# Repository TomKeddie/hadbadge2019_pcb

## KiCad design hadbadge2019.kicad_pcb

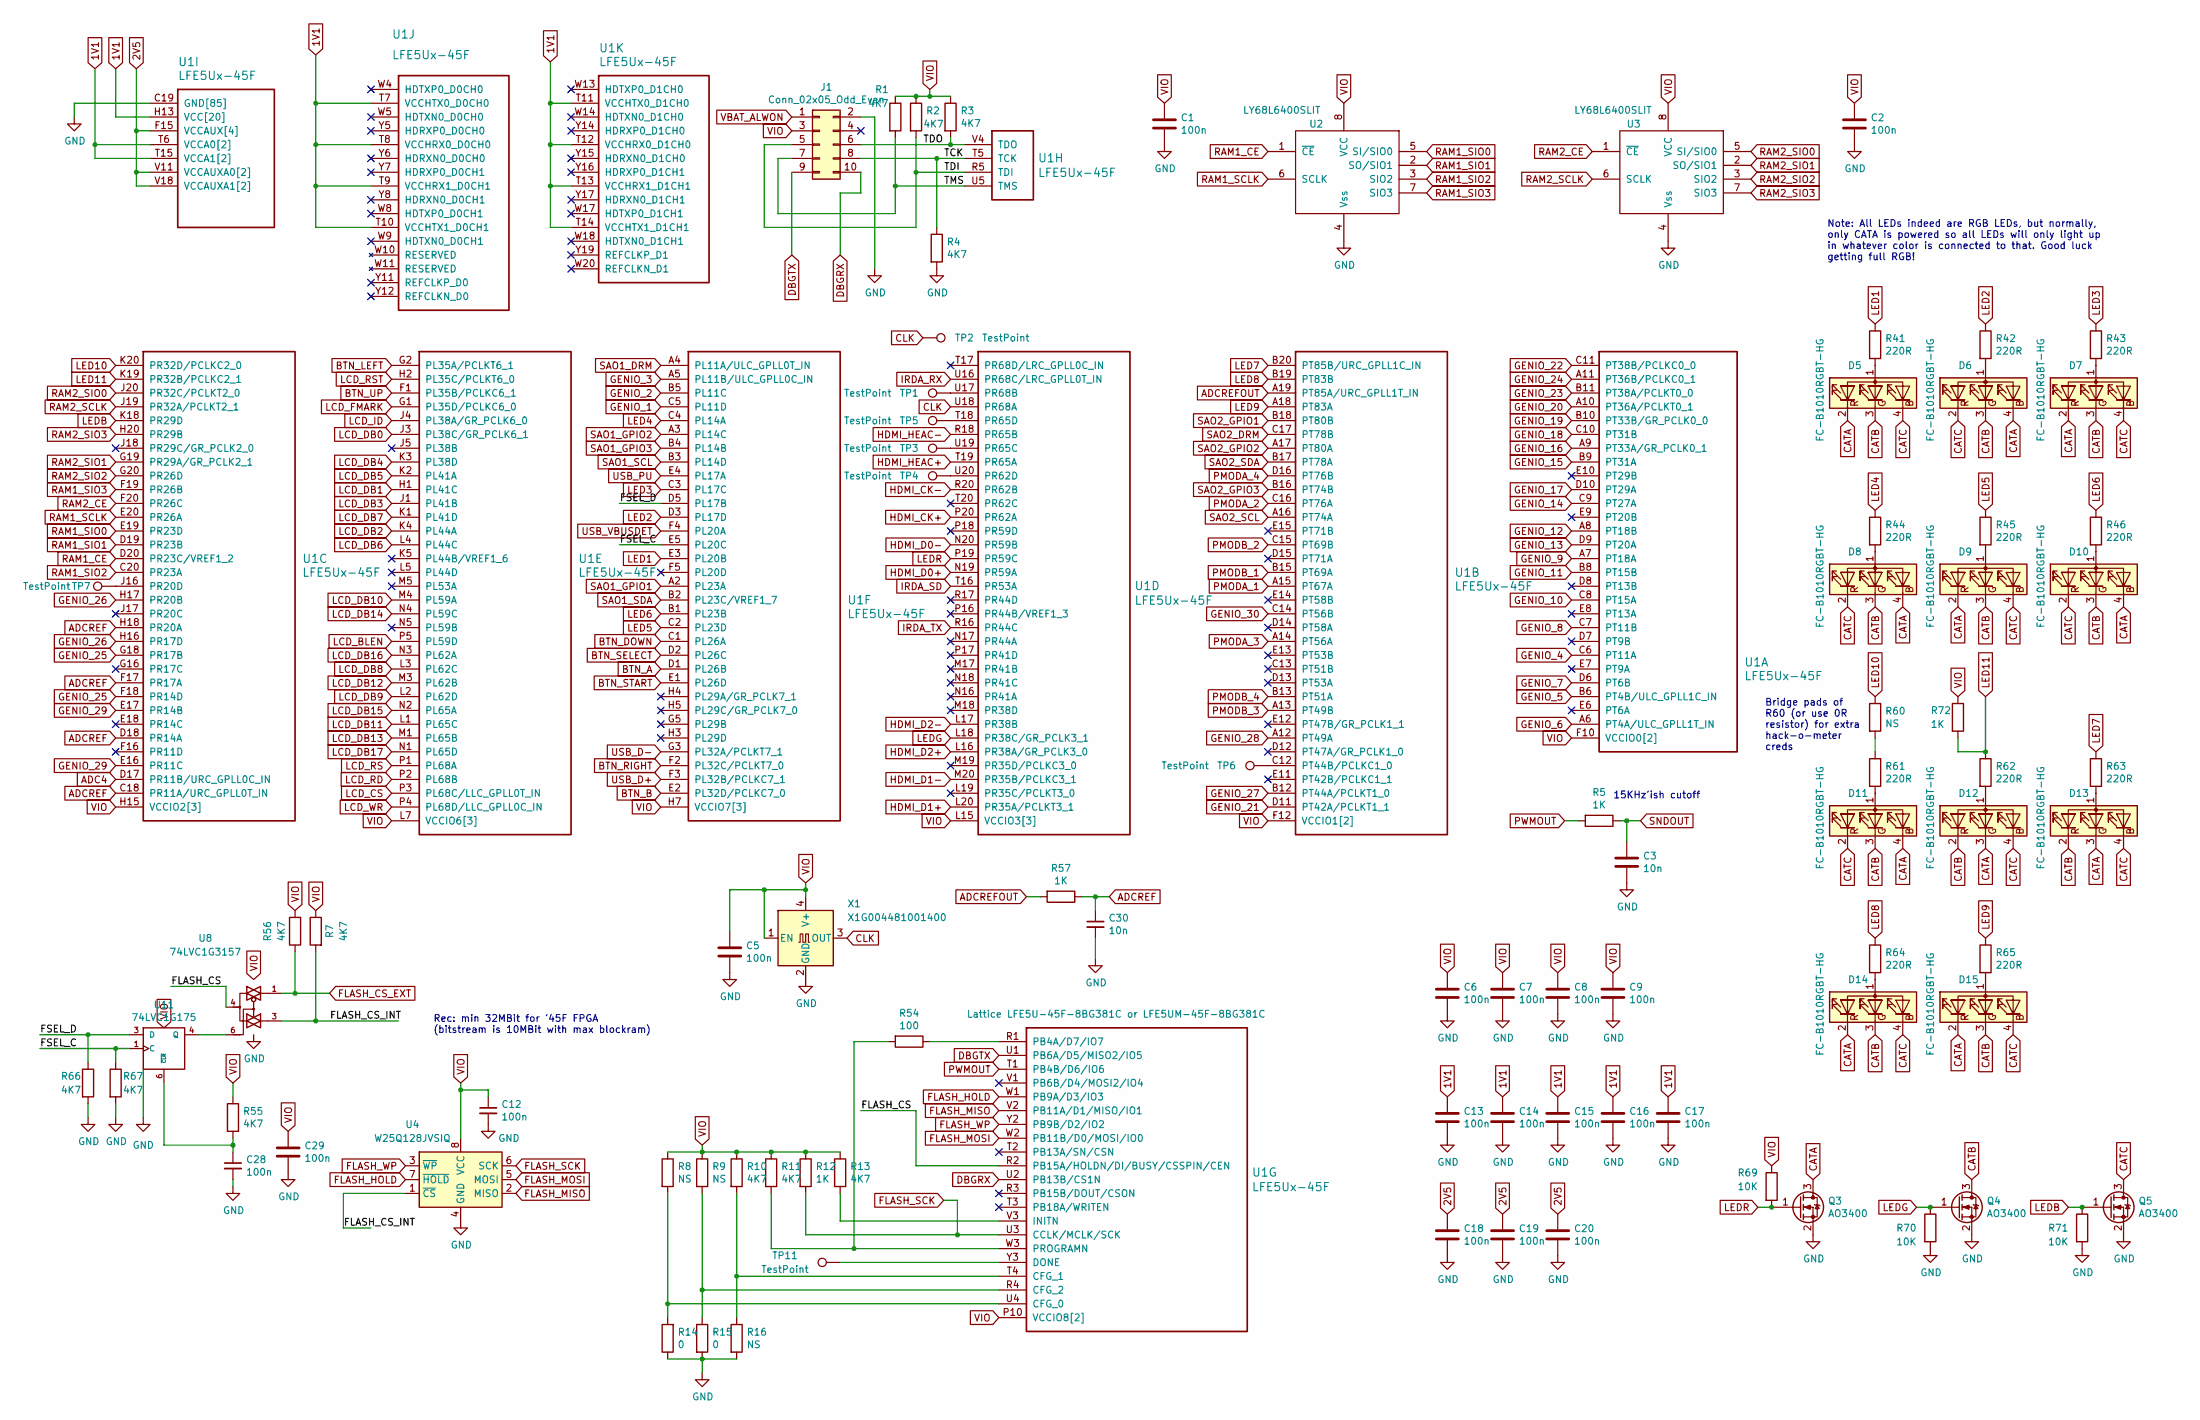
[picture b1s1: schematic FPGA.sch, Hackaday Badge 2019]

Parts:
C1, C2, C5, C6, C7, C8, C9, C12, C13, C14, C15, C16, C17, C18, C19, C20, C28, C29: 100n; C_0603_1608Metric
C3, C30: 10n; C_0603_1608Metric
D5, D6, D7, D8, D9, D10, D11, D12, D13, D14, D15: FC-B1010RGBT-HG
J1: Conn_02x05_Odd_Even; PinHeader_2x05_P2.54mm_Vertical
Q3, Q4, Q5: AO3400; SOT-23
R1, R2, R3, R4, R7, R10, R11, R13, R55, R56, R66, R67: 4K7; R_0603_1608Metric
R5, R12, R57, R72: 1K; R_0603_1608Metric
R8, R9, R16, R60: NS; R_0603_1608Metric
R14, R15: 0; R_0603_1608Metric
R41, R42, R43, R44, R45, R46, R61, R62, R63, R64, R65: 220R; R_0603_1608Metric
R54: 100; R_0603_1608Metric
R69, R70, R71: 10K; R_0603_1608Metric
TP1, TP2, TP3, TP4, TP5, TP6, TP7, TP11: TestPoint; TestPoint_Pad_D1.0mm
U1: LFE5Ux-45F; Lattice_caBGA-381_17.0x17.0mm_Layout20x20_P0.8mm_Ball0.4mm_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
U2, U3: LY68L6400SLIT; SSOP-8_3.9x5.05mm_P1.27mm
U4: W25Q128JVSIQ; SSOP-8_5.25x5.24mm_P1.27mm
U8: 74LVC1G3157; SOT-23-6
U11: 74LVC1G175; SOT-23-6
X1: X1G004481001400; Seiko_fp_crystal_SMD_7050-4Pin_7.0x5.0mm

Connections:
1V1: C13.1, C14.1, C15.1, C16.1, C17.1, U1.H8 (VCC[20]), U1.H9 (VCC[20]), U1.H10 (VCC[20]), U1.H11 (VCC[20]), U1.H12 (VCC[20]), U1.H13 (VCC[20]), U1.J8 (VCC[20]), U1.J13 (VCC[20]), U1.K8 (VCC[20]), U1.K13 (VCC[20]), U1.L8 (VCC[20]), U1.L13 (VCC[20]), U1.M8 (VCC[20]), U1.M13 (VCC[20]), U1.N8 (VCC[20]), U1.N9 (VCC[20]), U1.N10 (VCC[20]), U1.N11 (VCC[20]), U1.N12 (VCC[20]), U1.N13 (VCC[20]), U1.T6 (VCCA0[2]), U1.T7 (VCCHTX0_D0CH0), U1.T8 (VCCHRX0_D0CH0), U1.T9 (VCCHRX1_D0CH1), U1.T10 (VCCHTX1_D0CH1), U1.T11 (VCCHTX0_D1CH0), U1.T12 (VCCHRX0_D1CH0), U1.T13 (VCCHRX1_D1CH1), U1.T14 (VCCHTX1_D1CH1), U1.T15 (VCCA1[2]), U1.U6 (VCCA0[2]), U1.U15 (VCCA1[2]); also elsewhere on the board
2V5: C18.1, C19.1, C20.1, U1.F6 (VCCAUX[4]), U1.F15 (VCCAUX[4]), U1.P6 (VCCAUX[4]), U1.P15 (VCCAUX[4]), U1.V10 (VCCAUXA0[2]), U1.V11 (VCCAUXA0[2]), U1.V17 (VCCAUXA1[2]), U1.V18 (VCCAUXA1[2]); also elsewhere on the board
/FPGA/FLASH_CS: U1.R2 (PB15A/HOLDN/DI/BUSY/CSSPIN/CEN), U8.4
/FPGA/FLASH_CS_INT: R7.2, U4.1 (~CS), U8.3
/FPGA/FSEL_C: R67.1, U1.E5 (PL20C), U11.1 (C)
/FPGA/FSEL_D: R66.1, U1.D5 (PL17B), U11.3 (D)
/FPGA/TCK: J1.8, R4.1, U1.T5 (TCK)
/FPGA/TDI: J1.5, R2.2, U1.R5 (TDI)
/FPGA/TDO: J1.6, R3.2, U1.V4 (TDO)
/FPGA/TMS: J1.7, R1.2, U1.U5 (TMS)
ADC4: U1.D17 (PR11B/URC_GPLL0C_IN); also elsewhere on the board
ADCREF: C30.1, R57.1, U1.C18 (PR11A/URC_GPLL0T_IN), U1.D18 (PR14A), U1.F17 (PR17A), U1.H18 (PR20A)
ADCREFOUT: R57.2, U1.A19 (PT85A/URC_GPLL1T_IN)
BTN_A: U1.D1 (PL26B); also elsewhere on the board
BTN_B: U1.E2 (PL32D/PCLKC7_0); also elsewhere on the board
BTN_DOWN: U1.C1 (PL26A); also elsewhere on the board
BTN_LEFT: U1.G2 (PL35A/PCLKT6_1); also elsewhere on the board
BTN_RIGHT: U1.F2 (PL32C/PCLKT7_0); also elsewhere on the board
BTN_SELECT: U1.D2 (PL26C); also elsewhere on the board
BTN_START: U1.E1 (PL26D); also elsewhere on the board
BTN_UP: U1.F1 (PL35B/PCLKC6_1); also elsewhere on the board
CATA: D5.2 (RK), D6.4 (BK), D7.2 (RK), D8.4 (BK), D9.2 (RK), D10.4 (BK), D11.4 (BK), D12.3 (GK), D13.3 (GK), D14.2 (RK), D15.2 (RK), Q3.3 (D)
CATB: D5.3 (GK), D6.3 (GK), D7.3 (GK), D8.3 (GK), D9.3 (GK), D10.3 (GK), D11.3 (GK), D12.2 (RK), D13.2 (RK), D14.3 (GK), D15.3 (GK), Q4.3 (D)
CATC: D5.4 (BK), D6.2 (RK), D7.4 (BK), D8.2 (RK), D9.4 (BK), D10.2 (RK), D11.2 (RK), D12.4 (BK), D13.4 (BK), D14.4 (BK), D15.4 (BK), Q5.3 (D)
CLK: TP2.1, U1.U18 (PR68A), X1.3 (OUT)
DBGRX: J1.10, U1.U2 (PB13B/CS1N)
DBGTX: J1.9, U1.U1 (PB6A/D5/MISO2/IO5)
FLASH_CS_EXT: R56.1, U8.1; also elsewhere on the board
FLASH_HOLD: U1.W1 (PB9A/D3/IO3), U4.7 (~HOLD); also elsewhere on the board
FLASH_MISO: U1.V2 (PB11A/D1/MISO/IO1), U4.2 (MISO); also elsewhere on the board
FLASH_MOSI: U1.W2 (PB11B/D0/MOSI/IO0), U4.5 (MOSI); also elsewhere on the board
FLASH_SCK: R12.2, U1.U3 (CCLK/MCLK/SCK), U4.6 (SCK); also elsewhere on the board
FLASH_WP: U1.Y2 (PB9B/D2/IO2), U4.3 (~WP); also elsewhere on the board
GENIO_1: U1.C5 (PL11D); also elsewhere on the board
GENIO_2: U1.B5 (PL11C); also elsewhere on the board
GENIO_3: U1.A5 (PL11B/ULC_GPLL0C_IN); also elsewhere on the board
GENIO_4: U1.C6 (PT11A); also elsewhere on the board
GENIO_5: U1.B6 (PT4B/ULC_GPLL1C_IN); also elsewhere on the board
GENIO_6: U1.A6 (PT4A/ULC_GPLL1T_IN); also elsewhere on the board
GENIO_7: U1.D6 (PT6B); also elsewhere on the board
GENIO_8: U1.C7 (PT11B); also elsewhere on the board
GENIO_9: U1.A7 (PT18A); also elsewhere on the board
GENIO_10: U1.C8 (PT15A); also elsewhere on the board
GENIO_11: U1.B8 (PT15B); also elsewhere on the board
GENIO_12: U1.A8 (PT18B); also elsewhere on the board
GENIO_13: U1.D9 (PT20A); also elsewhere on the board
GENIO_14: U1.C9 (PT27A); also elsewhere on the board
GENIO_15: U1.B9 (PT31A); also elsewhere on the board
GENIO_16: U1.A9 (PT33A/GR_PCLK0_1); also elsewhere on the board
GENIO_17: U1.D10 (PT29A); also elsewhere on the board
GENIO_18: U1.C10 (PT31B); also elsewhere on the board
GENIO_19: U1.B10 (PT33B/GR_PCLK0_0); also elsewhere on the board
GENIO_20: U1.A10 (PT36A/PCLKT0_1); also elsewhere on the board
GENIO_21: U1.D11 (PT42A/PCLKT1_1); also elsewhere on the board
GENIO_22: U1.C11 (PT38B/PCLKC0_0); also elsewhere on the board
GENIO_23: U1.B11 (PT38A/PCLKT0_0); also elsewhere on the board
GENIO_24: U1.A11 (PT36B/PCLKC0_1); also elsewhere on the board
GENIO_25: U1.F18 (PR14D), U1.G18 (PR17B); also elsewhere on the board
GENIO_26: U1.H16 (PR17D), U1.H17 (PR20B); also elsewhere on the board
GENIO_27: U1.B12 (PT44A/PCLKT1_0); also elsewhere on the board
GENIO_28: U1.A12 (PT49A); also elsewhere on the board
GENIO_29: U1.E16 (PR11C), U1.E17 (PR14B); also elsewhere on the board
GENIO_30: U1.C14 (PT56B); also elsewhere on the board
GND: C1.2, C2.2, C3.2, C5.2, C6.2, C7.2, C8.2, C9.2, C12.2, C13.2, C14.2, C15.2, C16.2, C17.2, C18.2, C19.2, C20.2, C28.2, C29.2, C30.2, J1.2, Q3.2 (S), Q4.2 (S), Q5.2 (S), R4.2, R14.1, R15.2, R16.2, R66.2, R67.2, R70.2, R71.2, U1.B7 (GND[85]), U1.B14 (GND[85]), U1.C19 (GND[85]), U1.D4 (GND[85]), U1.F7 (GND[85]), U1.F8 (GND[85]), U1.F13 (GND[85]), U1.F14 (GND[85]), U1.G4 (GND[85]), U1.G6 (GND[85]), U1.G7 (GND[85]), U1.G8 (GND[85]), U1.G9 (GND[85]), U1.G10 (GND[85]), U1.G11 (GND[85]), U1.G12 (GND[85]), U1.G13 (GND[85]), U1.G14 (GND[85]), U1.G15 (GND[85]), U1.G17 (GND[85]), U1.H19 (GND[85]), U1.J2 (GND[85]), U1.J7 (GND[85]), U1.J9 (GND[85]), U1.J10 (GND[85]), U1.J11 (GND[85]), U1.J12 (GND[85]), U1.J14 (GND[85]), U1.K6 (GND[85]), U1.K7 (GND[85]), U1.K9 (GND[85]), U1.K10 (GND[85]), U1.K11 (GND[85]), U1.K12 (GND[85]), U1.K14 (GND[85]), U1.K15 (GND[85]), U1.L9 (GND[85]), U1.L10 (GND[85]), U1.L11 (GND[85]), U1.L12 (GND[85]), U1.M2 (GND[85]), U1.M7 (GND[85]), U1.M9 (GND[85]), U1.M10 (GND[85]), U1.M11 (GND[85]), U1.M12 (GND[85]), U1.M14 (GND[85]), U1.M16 (GND[85]), U1.N6 (GND[85]), U1.N7 (GND[85]), U1.N14 (GND[85]), U1.N15 (GND[85]), U1.P7 (GND[85]), U1.P8 (GND[85]), U1.P11 (GND[85]), U1.P12 (GND[85]), U1.P13 (GND[85]), U1.P14 (GND[85]), U1.R19 (GND[85]), U1.U7 (GND[85]), U1.U8 (GND[85]), U1.U9 (GND[85]), U1.U10 (GND[85]), U1.U11 (GND[85]), U1.U12 (GND[85]), U1.U13 (GND[85]), U1.U14 (GND[85]), U1.V5 (GND[85]), U1.V6 (GND[85]), U1.V7 (GND[85]), U1.V8 (GND[85]), U1.V9 (GND[85]), U1.V12 (GND[85]), U1.V13 (GND[85]), U1.V14 (GND[85]), U1.V15 (GND[85]), U1.V16 (GND[85]), U1.V19 (GND[85]), U1.V20 (GND[85]), U1.W6 (GND[85]), U1.W7 (GND[85]), U1.W12 (GND[85]), U1.W15 (GND[85]), U1.W16 (GND[85]), U1.W19 (GND[85]), U2.4 (Vss), U3.4 (Vss), U4.4 (GND), U8.2 (GND), U11.2 (GND), X1.2 (GND); also elsewhere on the board
HDMI_CK+: U1.P20 (PR62A); also elsewhere on the board
HDMI_CK-: U1.R20 (PR62B); also elsewhere on the board
HDMI_D0+: U1.N19 (PR59A); also elsewhere on the board
HDMI_D0-: U1.N20 (PR59B); also elsewhere on the board
HDMI_D1+: U1.L20 (PR35A/PCLKT3_1); also elsewhere on the board
HDMI_D1-: U1.M20 (PR35B/PCLKC3_1); also elsewhere on the board
HDMI_D2+: U1.L16 (PR38A/GR_PCLK3_0); also elsewhere on the board
HDMI_D2-: U1.L17 (PR38B); also elsewhere on the board
HDMI_HEAC+: U1.T19 (PR65A); also elsewhere on the board
HDMI_HEAC-: U1.R18 (PR65B); also elsewhere on the board
IRDA_RX: U1.U16 (PR68C/LRC_GPLL0T_IN); also elsewhere on the board
IRDA_SD: U1.T16 (PR53A); also elsewhere on the board
IRDA_TX: U1.R16 (PR44C); also elsewhere on the board
LCD_BLEN: U1.P5 (PL59D); also elsewhere on the board
LCD_CS: U1.P3 (PL68C/LLC_GPLL0T_IN); also elsewhere on the board
LCD_DB0: U1.J3 (PL38C/GR_PCLK6_1); also elsewhere on the board
LCD_DB1: U1.H1 (PL41C); also elsewhere on the board
LCD_DB2: U1.K4 (PL44A); also elsewhere on the board
LCD_DB3: U1.J1 (PL41B); also elsewhere on the board
LCD_DB4: U1.K3 (PL38D); also elsewhere on the board
LCD_DB5: U1.K2 (PL41A); also elsewhere on the board
LCD_DB6: U1.L4 (PL44C); also elsewhere on the board
LCD_DB7: U1.K1 (PL41D); also elsewhere on the board
LCD_DB8: U1.L3 (PL62C); also elsewhere on the board
LCD_DB9: U1.L2 (PL62D); also elsewhere on the board
LCD_DB10: U1.M4 (PL59A); also elsewhere on the board
LCD_DB11: U1.L1 (PL65C); also elsewhere on the board
LCD_DB12: U1.M3 (PL62B); also elsewhere on the board
LCD_DB13: U1.M1 (PL65B); also elsewhere on the board
LCD_DB14: U1.N4 (PL59C); also elsewhere on the board
LCD_DB15: U1.N2 (PL65A); also elsewhere on the board
LCD_DB16: U1.N3 (PL62A); also elsewhere on the board
LCD_DB17: U1.N1 (PL65D); also elsewhere on the board
LCD_FMARK: U1.G1 (PL35D/PCLKC6_0); also elsewhere on the board
LCD_ID: U1.J4 (PL38A/GR_PCLK6_0); also elsewhere on the board
LCD_RD: U1.P2 (PL68B); also elsewhere on the board
LCD_RS: U1.P1 (PL68A); also elsewhere on the board
LCD_RST: U1.H2 (PL35C/PCLKT6_0); also elsewhere on the board
LCD_WR: U1.P4 (PL68D/LLC_GPLL0C_IN); also elsewhere on the board
LED1: R41.1, U1.E3 (PL20B)
LED2: R42.1, U1.D3 (PL17D)
LED3: R43.1, U1.C3 (PL17C)
LED4: R44.1, U1.C4 (PL14A)
LED5: R45.1, U1.C2 (PL23D)
LED6: R46.1, U1.B1 (PL23B)
LED7: R63.1, U1.B20 (PT85B/URC_GPLL1C_IN)
LED8: R64.1, U1.B19 (PT83B)
LED9: R65.1, U1.A18 (PT83A)
LED10: R60.1, U1.K20 (PR32D/PCLKC2_0)
LED11: R62.1, R72.2, U1.K19 (PR32B/PCLKC2_1)
LEDB: Q5.1 (G), R71.1, U1.K18 (PR29D)
LEDG: Q4.1 (G), R70.1, U1.L18 (PR38C/GR_PCLK3_1)
LEDR: Q3.1 (G), R69.2, U1.P19 (PR59C)
unnamed: C28.1, R55.2, U11.6 (~CLR)
unnamed: D5.1 (A), R41.2
unnamed: D6.1 (A), R42.2
unnamed: D7.1 (A), R43.2
unnamed: D8.1 (A), R44.2
unnamed: D9.1 (A), R45.2
unnamed: D10.1 (A), R46.2
unnamed: D11.1 (A), R61.2
unnamed: D12.1 (A), R62.2
unnamed: D13.1 (A), R63.2
unnamed: D14.1 (A), R64.2
unnamed: D15.1 (A), R65.2
unnamed: R10.2, R16.1, U1.T4 (CFG_1)
unnamed: R11.2, R54.2, U1.W3 (PROGRAMN)
unnamed: R13.2, U1.V3 (INITN)
unnamed: R8.2, R14.2, U1.U4 (CFG_0)
unnamed: R9.2, R15.1, U1.R4 (CFG_2)
unnamed: R54.1, U1.R1 (PB4A/D7/IO7)
unnamed: R60.2, R61.1
unnamed: TP1.1, U1.U17 (PR68B)
unnamed: TP3.1, U1.U19 (PR65C)
unnamed: TP4.1, U1.U20 (PR62D)
unnamed: TP5.1, U1.T18 (PR65D)
unnamed: TP6.1, U1.C12 (PT44B/PCLKC1_0)
unnamed: TP7.1, U1.J16 (PR20D)
unnamed: TP11.1, U1.Y3 (DONE)
unnamed: U8.6, U11.4 (Q)
PMODA_1: U1.A15 (PT67A); also elsewhere on the board
PMODA_2: U1.C16 (PT76A); also elsewhere on the board
PMODA_3: U1.A14 (PT56A); also elsewhere on the board
PMODA_4: U1.D16 (PT76B); also elsewhere on the board
PMODB_1: U1.B15 (PT69A); also elsewhere on the board
PMODB_2: U1.C15 (PT69B); also elsewhere on the board
PMODB_3: U1.A13 (PT49B); also elsewhere on the board
PMODB_4: U1.B13 (PT51A); also elsewhere on the board
PWMOUT: R5.2, U1.T1 (PB4B/D6/IO6)
RAM1_CE: U1.D20 (PR23C/VREF1_2), U2.1 (~CE)
RAM1_SCLK: U1.E20 (PR26A), U2.6 (SCLK)
RAM1_SIO0: U1.E19 (PR23D), U2.5 (SI/SIO0)
RAM1_SIO1: U1.D19 (PR23B), U2.2 (SO/SIO1)
RAM1_SIO2: U1.C20 (PR23A), U2.3 (SIO2)
RAM1_SIO3: U1.F19 (PR26B), U2.7 (SIO3)
RAM2_CE: U1.F20 (PR26C), U3.1 (~CE)
RAM2_SCLK: U1.J19 (PR32A/PCLKT2_1), U3.6 (SCLK)
RAM2_SIO0: U1.J20 (PR32C/PCLKT2_0), U3.5 (SI/SIO0)
RAM2_SIO1: U1.G19 (PR29A/GR_PCLK2_1), U3.2 (SO/SIO1)
RAM2_SIO2: U1.G20 (PR26D), U3.3 (SIO2)
RAM2_SIO3: U1.H20 (PR29B), U3.7 (SIO3)
SAO1_DRM: U1.A4 (PL11A/ULC_GPLL0T_IN); also elsewhere on the board
SAO1_GPIO1: U1.A2 (PL23A); also elsewhere on the board
SAO1_GPIO2: U1.A3 (PL14C); also elsewhere on the board
SAO1_GPIO3: U1.B4 (PL14B); also elsewhere on the board
SAO1_SCL: U1.B3 (PL14D); also elsewhere on the board
SAO1_SDA: U1.B2 (PL23C/VREF1_7); also elsewhere on the board
SAO2_DRM: U1.C17 (PT78B); also elsewhere on the board
SAO2_GPIO1: U1.B18 (PT80B); also elsewhere on the board
SAO2_GPIO2: U1.A17 (PT80A); also elsewhere on the board
SAO2_GPIO3: U1.B16 (PT74B); also elsewhere on the board
SAO2_SCL: U1.A16 (PT74A); also elsewhere on the board
SAO2_SDA: U1.B17 (PT78A); also elsewhere on the board
SNDOUT: C3.1, R5.1; also elsewhere on the board
USB_D+: U1.F3 (PL32B/PCLKC7_1); also elsewhere on the board
USB_D-: U1.G3 (PL32A/PCLKT7_1); also elsewhere on the board
USB_PU: U1.E4 (PL17A); also elsewhere on the board
USB_VBUSDET: U1.F4 (PL20A); also elsewhere on the board
VBAT_ALWON: J1.1; also elsewhere on the board
VIO: C1.1, C2.1, C5.1, C6.1, C7.1, C8.1, C9.1, C12.1, C29.1, J1.3, R1.1, R2.1, R3.1, R7.1, R8.1, R9.1, R10.1, R11.1, R12.1, R13.1, R55.1, R56.2, R69.1, R72.1, U1.F9 (VCCIO0[2]), U1.F10 (VCCIO0[2]), U1.F11 (VCCIO1[2]), U1.F12 (VCCIO1[2]), U1.H6 (VCCIO7[3]), U1.H7 (VCCIO7[3]), U1.H14 (VCCIO2[3]), U1.H15 (VCCIO2[3]), U1.J6 (VCCIO7[3]), U1.J15 (VCCIO2[3]), U1.L6 (VCCIO6[3]), U1.L7 (VCCIO6[3]), U1.L14 (VCCIO3[3]), U1.L15 (VCCIO3[3]), U1.M6 (VCCIO6[3]), U1.M15 (VCCIO3[3]), U1.P9 (VCCIO8[2]), U1.P10 (VCCIO8[2]), U2.8 (VCC), U3.8 (VCC), U4.8 (VCC), U8.5 (VCC), U11.5 (VCC), X1.1 (EN), X1.4 (V+); also elsewhere on the board

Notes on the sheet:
Rec: min 32MBit for '45F FPGA (bitstream is 10MBit with max blockram)
15KHz'ish cutoff
Note: All LEDs indeed are RGB LEDs, but normally, only CATA is powered so all LEDs will only light up in whatever color is connected to that. Good luck getting full RGB!
Bridge pads of R60 (or use 0R resistor) for extra hack-o-meter creds

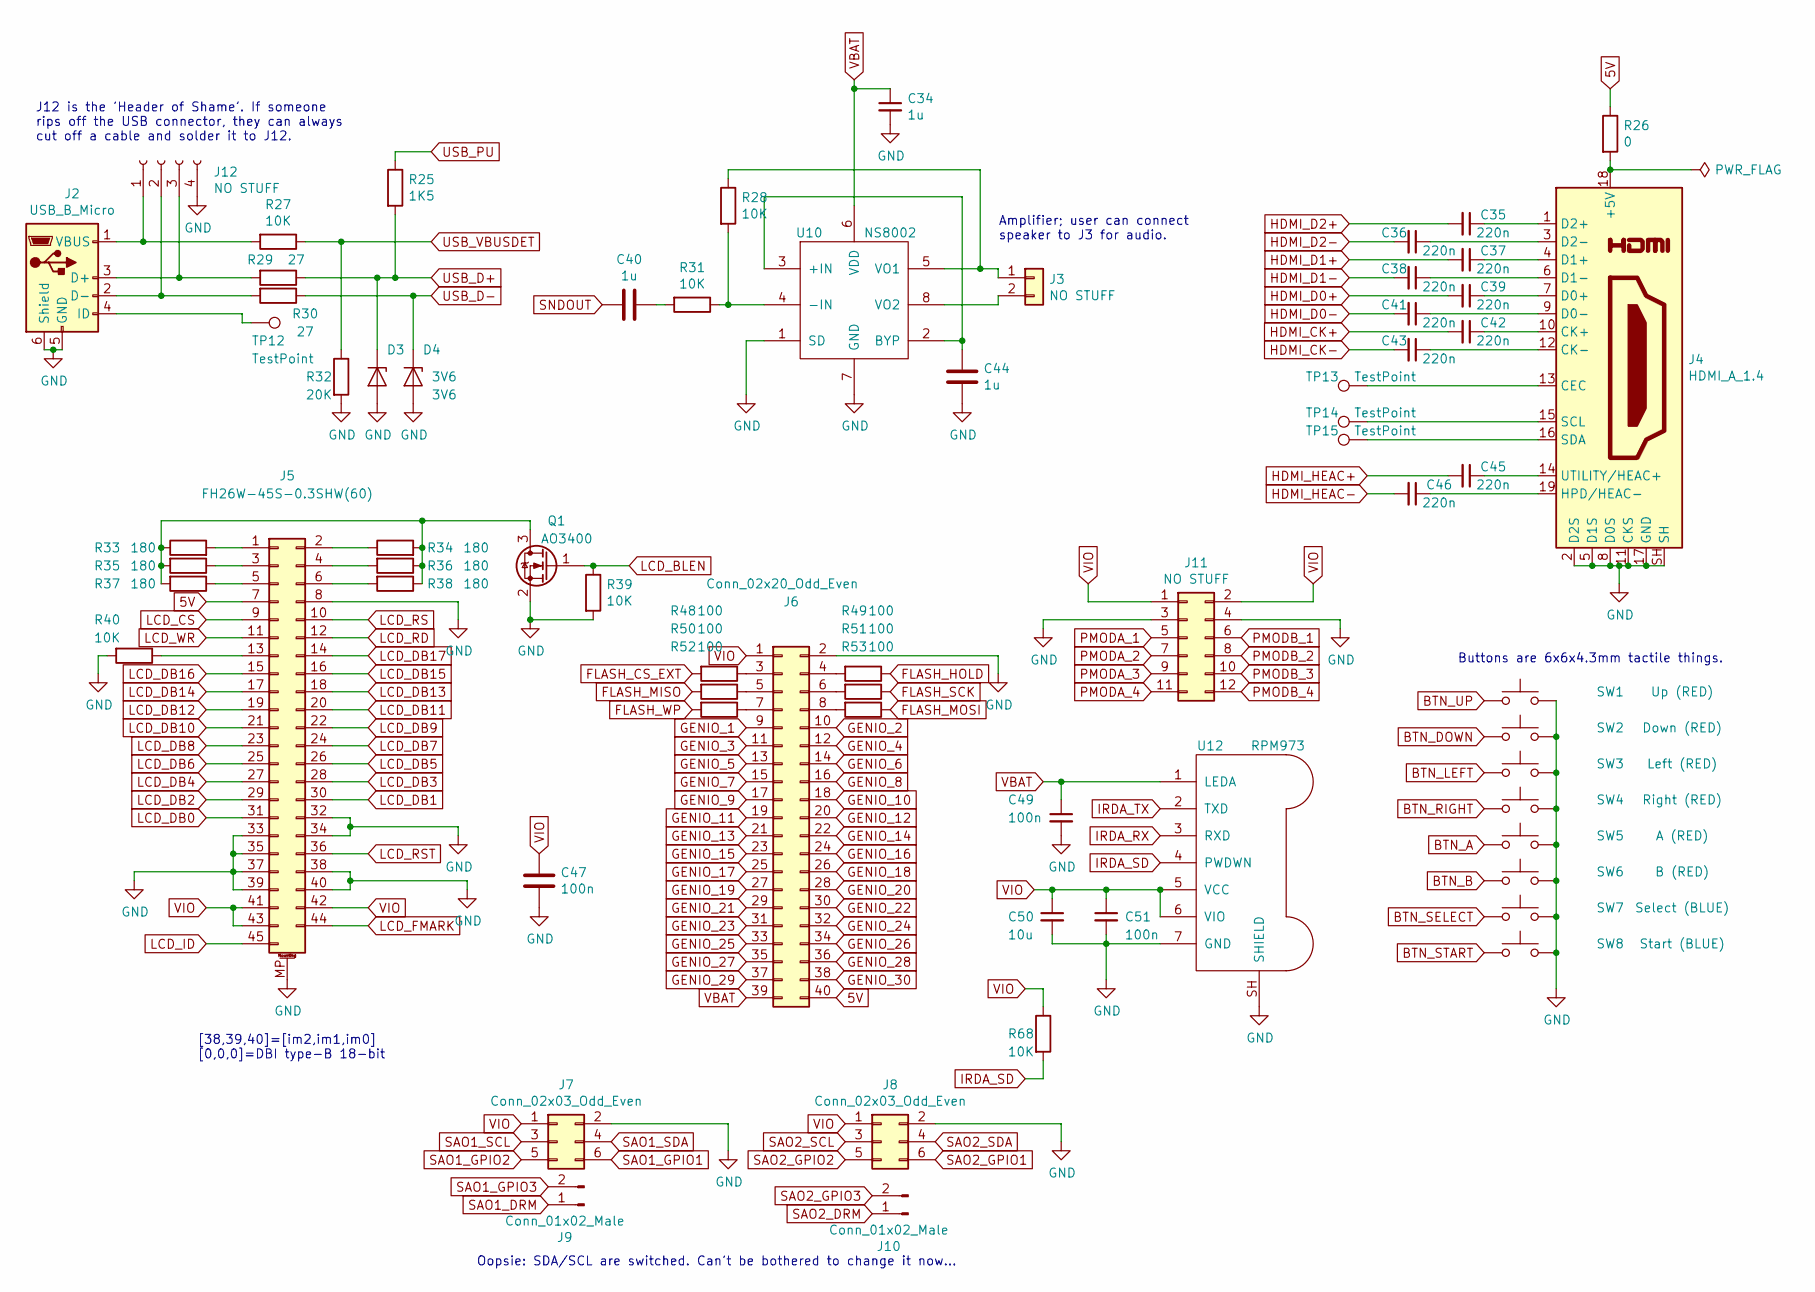
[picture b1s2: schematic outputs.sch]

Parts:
C34, C40, C44: 1u; C_0603_1608Metric
C35, C36, C37, C38, C39, C41, C42, C43, C45, C46: 220n; C_0603_1608Metric
C47, C49, C51: 100n; C_0603_1608Metric
C50: 10u; C_0805_2012Metric
D3, D4: 3V6; D_SOD-323
J2: USB_B_Micro; USB_Micro-B_China_MK5P
J3: NO STUFF; PinSocket_1x02_P2.54mm_Vertical
J4: HDMI_A_1.4; Boom_Precision_HDMI-001
J5: FH26W-45S-0.3SHW(60); FH26-45S-0.3SHW
J6: Conn_02x20_Odd_Even; PinSocket_2x20_P2.54mm_Horizontal
J7, J8: Conn_02x03_Odd_Even; PinSocket_2x03_P2.54mm_Vertical
J9, J10: Conn_01x02_Male; PinHeader_1x02_P2.54mm_Vertical
J11: NO STUFF; PinSocket_2x06_P2.54mm_Horizontal
J12: NO STUFF; PinHeader_1x04_P2.54mm_Vertical
Q1: AO3400; SOT-23
R25: 1K5; R_0603_1608Metric
R26: 0; R_0603_1608Metric
R27, R28, R31, R39, R40, R68: 10K; R_0603_1608Metric
R29, R30: 27; R_0603_1608Metric
R32: 20K; R_0603_1608Metric
R33, R34, R35, R36, R37, R38: 180; R_0603_1608Metric
R48, R49, R50, R51, R52, R53: 100; R_0603_1608Metric
SW1: Up (RED); SW_Push_1P1T_NO_6x6mm_H9.5mm
SW2: Down (RED); SW_Push_1P1T_NO_6x6mm_H9.5mm
SW3: Left (RED); SW_Push_1P1T_NO_6x6mm_H9.5mm
SW4: Right (RED); SW_Push_1P1T_NO_6x6mm_H9.5mm
SW5: A (RED); SW_Push_1P1T_NO_6x6mm_H9.5mm
SW6: B (RED); SW_Push_1P1T_NO_6x6mm_H9.5mm
SW7: Select (BLUE); SW_Push_1P1T_NO_6x6mm_H9.5mm
SW8: Start (BLUE); SW_Push_1P1T_NO_6x6mm_H9.5mm
TP12, TP13, TP14, TP15: TestPoint; TestPoint_Pad_D1.0mm
U10: NS8002; SSOP-8_3.9x5.05mm_P1.27mm
U12: RPM973; RPM973-H11

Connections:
5V: J5.7, J6.40, R26.1; also elsewhere on the board
BTN_A: SW5.1; also elsewhere on the board
BTN_B: SW6.1; also elsewhere on the board
BTN_DOWN: SW2.1; also elsewhere on the board
BTN_LEFT: SW3.1; also elsewhere on the board
BTN_RIGHT: SW4.1; also elsewhere on the board
BTN_SELECT: SW7.1; also elsewhere on the board
BTN_START: SW8.1; also elsewhere on the board
BTN_UP: SW1.1; also elsewhere on the board
FLASH_CS_EXT: R48.2; also elsewhere on the board
FLASH_HOLD: R49.1; also elsewhere on the board
FLASH_MISO: R50.2; also elsewhere on the board
FLASH_MOSI: R53.1; also elsewhere on the board
FLASH_SCK: R51.1; also elsewhere on the board
FLASH_WP: R52.2; also elsewhere on the board
GENIO_1: J6.9; also elsewhere on the board
GENIO_2: J6.10; also elsewhere on the board
GENIO_3: J6.11; also elsewhere on the board
GENIO_4: J6.12; also elsewhere on the board
GENIO_5: J6.13; also elsewhere on the board
GENIO_6: J6.14; also elsewhere on the board
GENIO_7: J6.15; also elsewhere on the board
GENIO_8: J6.16; also elsewhere on the board
GENIO_9: J6.17; also elsewhere on the board
GENIO_10: J6.18; also elsewhere on the board
GENIO_11: J6.19; also elsewhere on the board
GENIO_12: J6.20; also elsewhere on the board
GENIO_13: J6.21; also elsewhere on the board
GENIO_14: J6.22; also elsewhere on the board
GENIO_15: J6.23; also elsewhere on the board
GENIO_16: J6.24; also elsewhere on the board
GENIO_17: J6.25; also elsewhere on the board
GENIO_18: J6.26; also elsewhere on the board
GENIO_19: J6.27; also elsewhere on the board
GENIO_20: J6.28; also elsewhere on the board
GENIO_21: J6.29; also elsewhere on the board
GENIO_22: J6.30; also elsewhere on the board
GENIO_23: J6.31; also elsewhere on the board
GENIO_24: J6.32; also elsewhere on the board
GENIO_25: J6.33; also elsewhere on the board
GENIO_26: J6.34; also elsewhere on the board
GENIO_27: J6.35; also elsewhere on the board
GENIO_28: J6.36; also elsewhere on the board
GENIO_29: J6.37; also elsewhere on the board
GENIO_30: J6.38; also elsewhere on the board
GND: C34.2, C44.2, C47.2, C49.2, C50.2, C51.2, D3.2 (A), D4.2 (A), J2.5 (GND), J2.6 (Shield), J4.2 (D2S), J4.5 (D1S), J4.8 (D0S), J4.11 (CKS), J4.17 (GND), J4.SH, J5.8, J5.32, J5.33, J5.34, J5.35, J5.37, J5.38, J5.39, J5.40, J5.MP (MountPin), J6.2, J7.2, J8.2, J11.3, J11.4, J12.4, Q1.2 (S), R32.2, R39.2, R40.2, SW1.2, SW2.2, SW3.2, SW4.2, SW5.2, SW6.2, SW7.2, SW8.2, U10.1 (SD), U10.7 (GND), U12.7 (GND), U12.SH (SHIELD); also elsewhere on the board
HDMI_CK+: C42.2; also elsewhere on the board
HDMI_CK-: C43.2; also elsewhere on the board
HDMI_D0+: C39.2; also elsewhere on the board
HDMI_D0-: C41.2; also elsewhere on the board
HDMI_D1+: C37.2; also elsewhere on the board
HDMI_D1-: C38.2; also elsewhere on the board
HDMI_D2+: C35.2; also elsewhere on the board
HDMI_D2-: C36.2; also elsewhere on the board
HDMI_HEAC+: C45.2; also elsewhere on the board
HDMI_HEAC-: C46.2; also elsewhere on the board
IRDA_RX: U12.3 (RXD); also elsewhere on the board
IRDA_SD: R68.2, U12.4 (PWDWN); also elsewhere on the board
IRDA_TX: U12.2 (TXD); also elsewhere on the board
LCD_BLEN: Q1.1 (G), R39.1; also elsewhere on the board
LCD_CS: J5.9; also elsewhere on the board
LCD_DB0: J5.31; also elsewhere on the board
LCD_DB1: J5.30; also elsewhere on the board
LCD_DB2: J5.29; also elsewhere on the board
LCD_DB3: J5.28; also elsewhere on the board
LCD_DB4: J5.27; also elsewhere on the board
LCD_DB5: J5.26; also elsewhere on the board
LCD_DB6: J5.25; also elsewhere on the board
LCD_DB7: J5.24; also elsewhere on the board
LCD_DB8: J5.23; also elsewhere on the board
LCD_DB9: J5.22; also elsewhere on the board
LCD_DB10: J5.21; also elsewhere on the board
LCD_DB11: J5.20; also elsewhere on the board
LCD_DB12: J5.19; also elsewhere on the board
LCD_DB13: J5.18; also elsewhere on the board
LCD_DB14: J5.17; also elsewhere on the board
LCD_DB15: J5.16; also elsewhere on the board
LCD_DB16: J5.15; also elsewhere on the board
LCD_DB17: J5.14; also elsewhere on the board
LCD_FMARK: J5.44; also elsewhere on the board
LCD_ID: J5.45; also elsewhere on the board
LCD_RD: J5.12; also elsewhere on the board
LCD_RS: J5.10; also elsewhere on the board
LCD_RST: J5.36; also elsewhere on the board
LCD_WR: J5.11; also elsewhere on the board
unnamed: C35.1, J4.1 (D2+)
unnamed: C36.1, J4.3 (D2-)
unnamed: C37.1, J4.4 (D1+)
unnamed: C38.1, J4.6 (D1-)
unnamed: C39.1, J4.7 (D0+)
unnamed: C40.1, R31.2
unnamed: C41.1, J4.9 (D0-)
unnamed: C42.1, J4.10 (CK+)
unnamed: C43.1, J4.12 (CK-)
unnamed: C44.1, U10.2 (BYP), U10.3 (+IN)
unnamed: C45.1, J4.14 (UTILITY/HEAC+)
unnamed: C46.1, J4.19 (HPD/HEAC-)
unnamed: J2.4 (ID), TP12.1
unnamed: J3.1, R28.1, U10.5 (VO1)
unnamed: J3.2, U10.8 (VO2)
unnamed: J4.13 (CEC), TP13.1
unnamed: J4.15 (SCL), TP14.1
unnamed: J4.16 (SDA), TP15.1
unnamed: J4.18 (+5V), R26.2
unnamed: J5.1, R33.2
unnamed: J5.2, R34.1
unnamed: J5.3, R35.1
unnamed: J5.4, R36.2
unnamed: J5.5, R37.1
unnamed: J5.6, R38.2
unnamed: J5.13, R40.1
unnamed: J6.3, R48.1
unnamed: J6.4, R49.2
unnamed: J6.5, R50.1
unnamed: J6.6, R51.2
unnamed: J6.7, R52.1
unnamed: J6.8, R53.2
unnamed: J2.1 (VBUS), J12.1, R27.2
unnamed: J2.2 (D-), J12.2, R30.2
unnamed: J2.3 (D+), J12.3, R29.2
unnamed: Q1.3 (D), R33.1, R34.2, R35.2, R36.1, R37.2, R38.1
unnamed: R28.2, R31.1, U10.4 (-IN)
PMODA_1: J11.5; also elsewhere on the board
PMODA_2: J11.7; also elsewhere on the board
PMODA_3: J11.9; also elsewhere on the board
PMODA_4: J11.11; also elsewhere on the board
PMODB_1: J11.6; also elsewhere on the board
PMODB_2: J11.8; also elsewhere on the board
PMODB_3: J11.10; also elsewhere on the board
PMODB_4: J11.12; also elsewhere on the board
SAO1_DRM: J9.1; also elsewhere on the board
SAO1_GPIO1: J7.6; also elsewhere on the board
SAO1_GPIO2: J7.5; also elsewhere on the board
SAO1_GPIO3: J9.2; also elsewhere on the board
SAO1_SCL: J7.3; also elsewhere on the board
SAO1_SDA: J7.4; also elsewhere on the board
SAO2_DRM: J10.1; also elsewhere on the board
SAO2_GPIO1: J8.6; also elsewhere on the board
SAO2_GPIO2: J8.5; also elsewhere on the board
SAO2_GPIO3: J10.2; also elsewhere on the board
SAO2_SCL: J8.3; also elsewhere on the board
SAO2_SDA: J8.4; also elsewhere on the board
SNDOUT: C40.2; also elsewhere on the board
USB_D+: D3.1 (K), R25.2, R29.1; also elsewhere on the board
USB_D-: D4.1 (K), R30.1; also elsewhere on the board
USB_PU: R25.1; also elsewhere on the board
USB_VBUSDET: R27.1, R32.1; also elsewhere on the board
VBAT: C34.1, C49.1, J6.39, U10.6 (VDD), U12.1 (LEDA); also elsewhere on the board
VIO: C47.1, C50.1, C51.1, J5.41, J5.42, J5.43, J6.1, J7.1, J8.1, J11.1, J11.2, R68.1, U12.5 (VCC), U12.6 (VIO); also elsewhere on the board

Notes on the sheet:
[38,39,40]=[im2,im1,im0] [0,0,0]=DBI type-B 18-bit
Amplifier; user can connect speaker to J3 for audio.
J12 is the 'Header of Shame'. If someone rips off the USB connector, they can always cut off a cable and solder it to J12.
Buttons are 6x6x4.3mm tactile things.
Oopsie: SDA/SCL are switched. Can't be bothered to change it now...

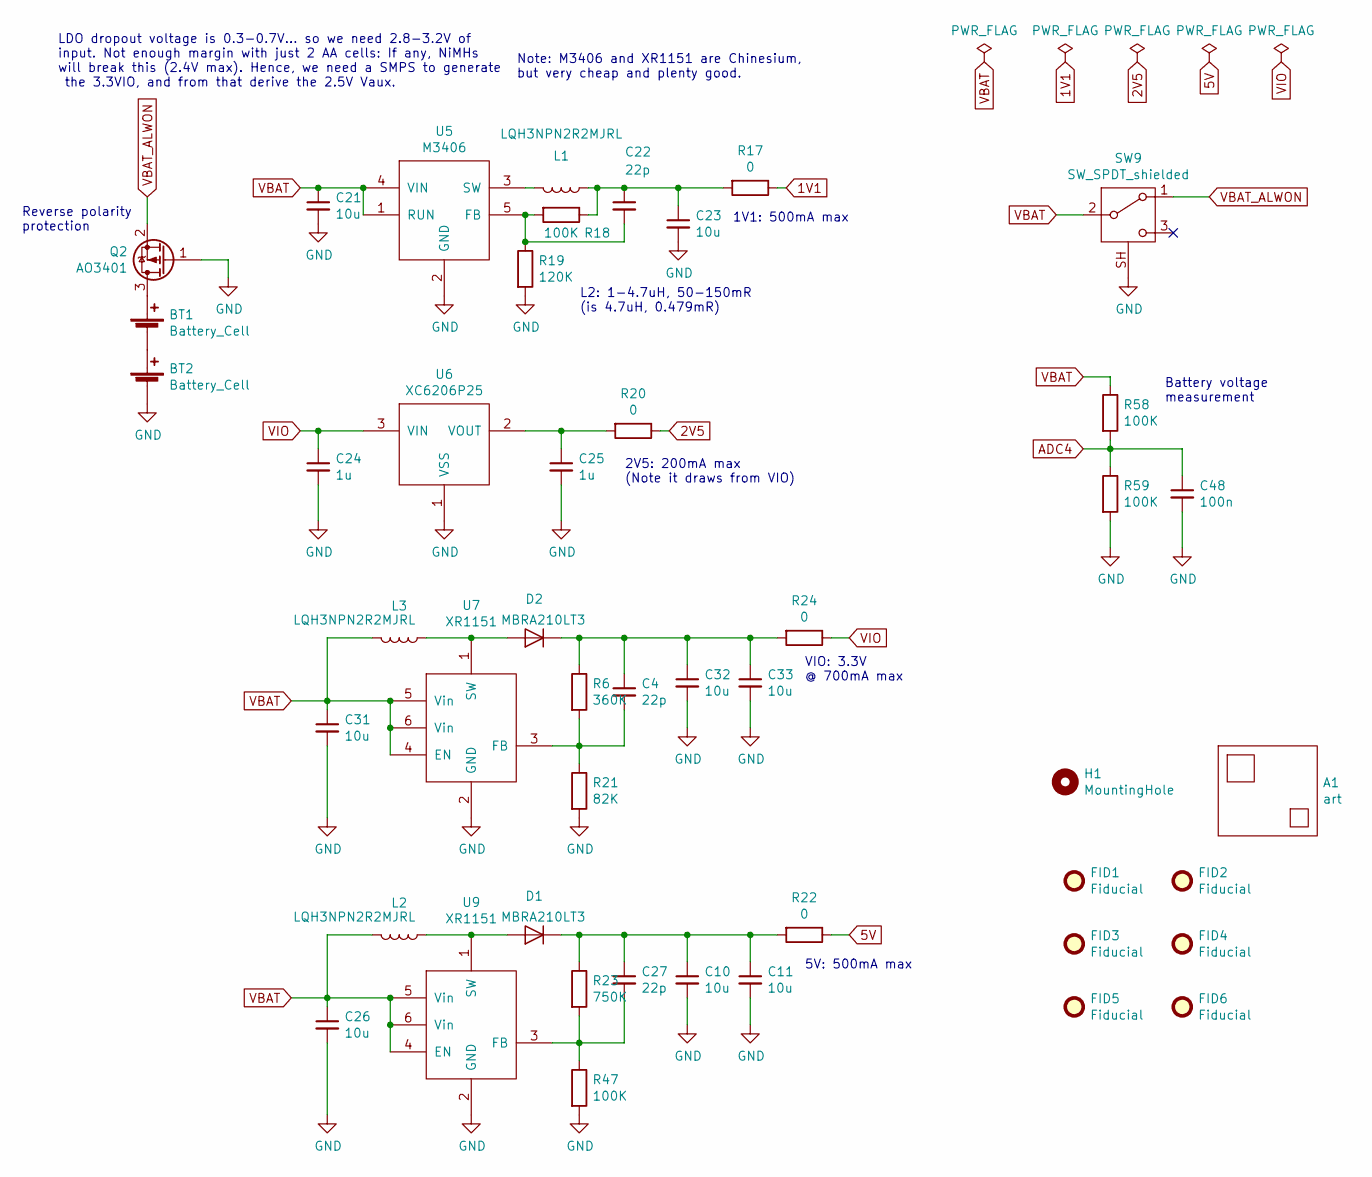
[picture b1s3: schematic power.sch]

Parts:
A1: art; badge_art
BT1, BT2: Battery_Cell; battery_holder_1xAA
C4, C22, C27: 22p; C_0603_1608Metric
C10, C11, C21, C23, C26, C31, C32, C33: 10u; C_0805_2012Metric
C24, C25: 1u; C_0603_1608Metric
C48: 100n; C_0603_1608Metric
D1, D2: MBRA210LT3; D_SMA
FID1, FID2, FID3, FID4, FID5, FID6: Fiducial; Fiducial_0.75mm_Mask1.5mm
H1: MountingHole; MountingHole_3.5mm
L1, L2, L3: LQH3NPN2R2MJRL; Murata_1212
Q2: AO3401; SOT-23
R6: 360K; R_0603_1608Metric
R17, R20, R22, R24: 0; R_0603_1608Metric
R18, R47, R58, R59: 100K; R_0603_1608Metric
R19: 120K; R_0603_1608Metric
R21: 82K; R_0603_1608Metric
R23: 750K; R_0603_1608Metric
SW9: SW_SPDT_shielded; Korean_Hroparts_K3_1296S
U5: M3406; SOT-23-5
U6: XC6206P25; SOT-23
U7, U9: XR1151; SOT-23-6

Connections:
1V1: R17.1; also elsewhere on the board
2V5: R20.1; also elsewhere on the board
5V: R22.1; also elsewhere on the board
ADC4: C48.1, R58.2, R59.1; also elsewhere on the board
GND: BT2.2 (-), C10.2, C11.2, C21.2, C23.2, C24.2, C25.2, C26.2, C31.2, C32.2, C33.2, C48.2, Q2.1 (G), R19.2, R21.2, R47.2, R59.2, SW9.SH, U5.2 (GND), U6.1 (VSS), U7.2 (GND), U9.2 (GND); also elsewhere on the board
unnamed: BT1.1 (+), Q2.3 (D)
unnamed: BT1.2 (-), BT2.1 (+)
unnamed: C4.2, R6.2, R21.1, U7.3 (FB)
unnamed: C10.1, C11.1, C27.1, D1.1 (K), R22.2, R23.1
unnamed: C22.1, C23.1, L1.1, R17.2, R18.1
unnamed: C22.2, R18.2, R19.1, U5.5 (FB)
unnamed: C25.1, R20.2, U6.2 (VOUT)
unnamed: C27.2, R23.2, R47.1, U9.3 (FB)
unnamed: C4.1, C32.1, C33.1, D2.1 (K), R6.1, R24.2
unnamed: D1.2 (A), L2.1, U9.1 (SW)
unnamed: D2.2 (A), L3.1, U7.1 (SW)
unnamed: L1.2, U5.3 (SW)
VBAT: C21.1, C26.1, C31.1, L2.2, L3.2, R58.1, SW9.2 (B), U5.1 (RUN), U5.4 (VIN), U7.4 (EN), U7.5 (Vin), U7.6 (Vin), U9.4 (EN), U9.5 (Vin), U9.6 (Vin); also elsewhere on the board
VBAT_ALWON: Q2.2 (S), SW9.1 (A); also elsewhere on the board
VIO: C24.1, R24.1, U6.3 (VIN); also elsewhere on the board

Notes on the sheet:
LDO dropout voltage is 0.3-0.7V... so we need 2.8-3.2V of input. Not enough margin with just 2 AA cells: If any, NiMHs will break this (2.4V max). Hence, we need a SMPS to generate the 3.3VIO, and from that derive the 2.5V Vaux.
Note: M3406 and XR1151 are Chinesium, but very cheap and plenty good.
1V1: 500mA max
2V5: 200mA max (Note it draws from VIO)
L2: 1-4.7uH, 50-150mR (is 4.7uH, 0.479mR)
VIO: 3.3V @ 700mA max
5V: 500mA max
Reverse polarity protection
Battery voltage measurement
